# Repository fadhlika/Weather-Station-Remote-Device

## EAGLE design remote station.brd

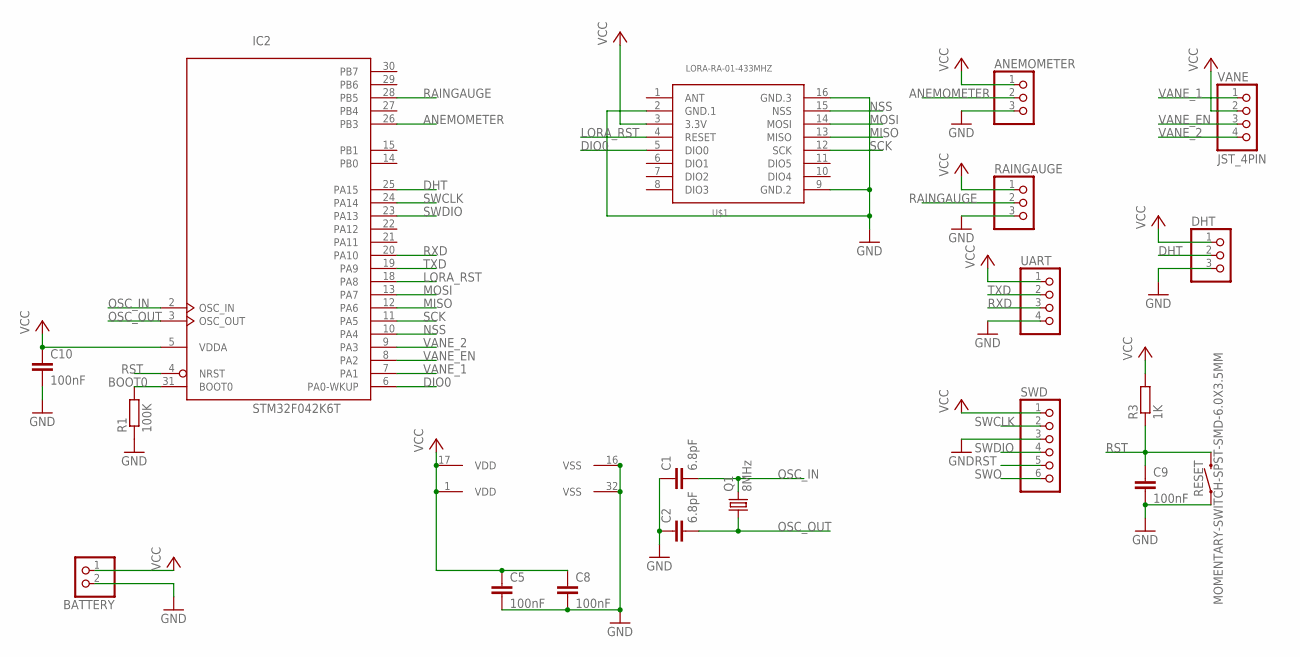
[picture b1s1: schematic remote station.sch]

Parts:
ANEMOMETER: JST_3PIN; JSTPH3
BATTERY: JST_2PIN-SMT-RA; JST-PH-2-SMT-RA
C1, C2: 6.8pF; C0805K
C5, C8, C9, C10: 100nF; C0805K
DHT: JST_3PIN; JSTPH3
IC2: STM32F042K6T; LQFP32
Q1: 8MHz; HC49UP
R1: 100K; R0805W
R3: 1K; R0805W
RAINGAUGE: JST_3PIN; JSTPH3
RESET: MOMENTARY-SWITCH-SPST-SMD-6.0X3.5MM; TACTILE_SWITCH_SMD_6.0X3.5MM
SWD: PINHD-1X6; 1X06
U$1: LORA-RA-01-433MHZ; LORA-RA1-SMD
UART: PINHD-1X4; 1X04
VANE: JST_4PIN; JST-PH-2-SMT-RA

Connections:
ANEMOMETER: ANEMOMETER.2, IC2.26 (PB3)
BOOT0: IC2.31 (BOOT0), R1.2
DHT: DHT.2, IC2.25 (PA15)
DIO0: IC2.6 (PA0-WKUP), U$1.5 (DIO0)
GND: ANEMOMETER.3, BATTERY.2 (1), C1.1, C2.1, C5.2, C8.2, C9.2, C10.2, DHT.3, IC2.16 (VSS), IC2.32 (VSS), R1.1, RAINGAUGE.3, RESET.1, SWD.3, U$1.2 (GND.1), U$1.9 (GND.2), U$1.16 (GND.3), UART.4
LORA_RST: IC2.18 (PA8), U$1.4 (RESET)
MISO: IC2.12 (PA6), U$1.13 (MISO)
MOSI: IC2.13 (PA7), U$1.14 (MOSI)
NSS: IC2.10 (PA4), U$1.15 (NSS)
OSC_IN: C1.2, IC2.2 (OSC_IN), Q1.2
OSC_OUT: C2.2, IC2.3 (OSC_OUT), Q1.1
RAINGAUGE: IC2.28 (PB5), RAINGAUGE.2
RST: C9.1, IC2.4 (NRST), R3.1, RESET.2, SWD.5
RXD: IC2.20 (PA10), UART.3
SCK: IC2.11 (PA5), U$1.12 (SCK)
SWCLK: IC2.24 (PA14), SWD.2
SWDIO: IC2.23 (PA13), SWD.4
SWO: SWD.6
TXD: IC2.19 (PA9), UART.2
VANE_1: IC2.7 (PA1), VANE.1
VANE_2: IC2.9 (PA3), VANE.4
VANE_EN: IC2.8 (PA2), VANE.3
VCC: ANEMOMETER.1, BATTERY.1 (2), C5.1, C8.1, C10.1, DHT.1, IC2.1 (VDD), IC2.5 (VDDA), IC2.17 (VDD), R3.2, RAINGAUGE.1, SWD.1, U$1.3 (3.3V), UART.1, VANE.2

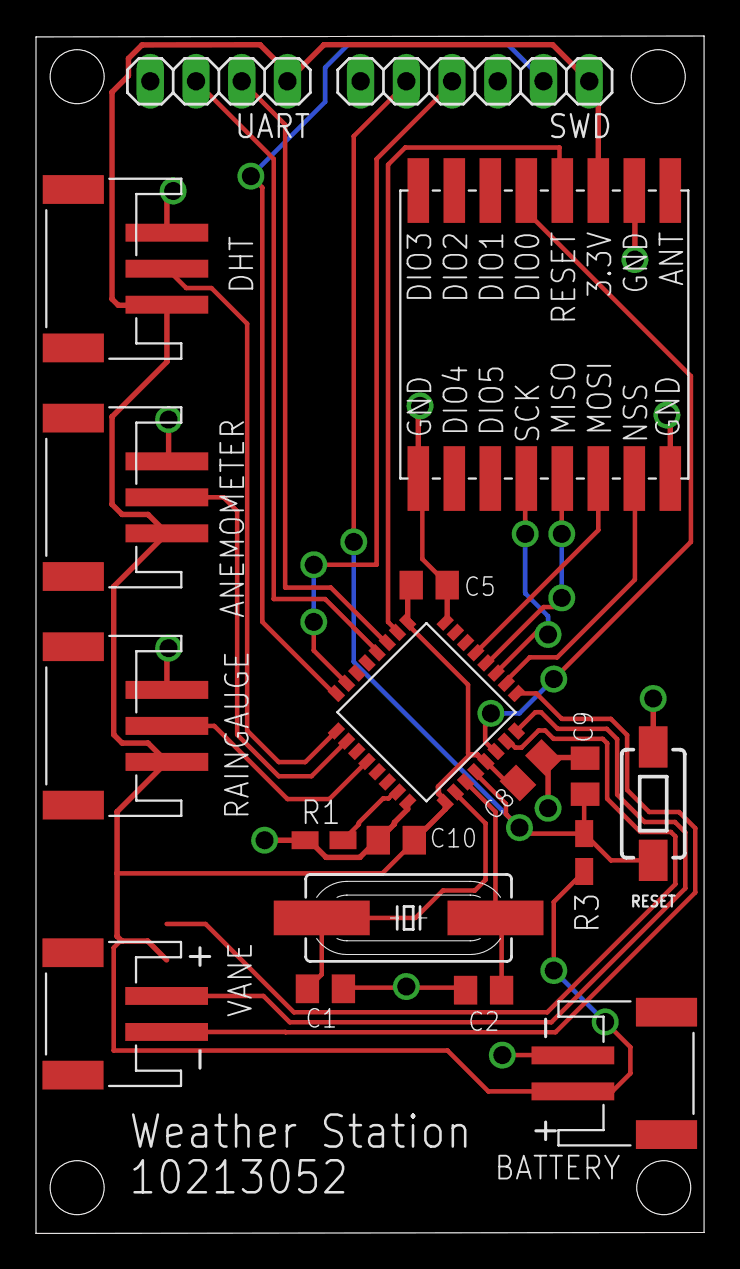
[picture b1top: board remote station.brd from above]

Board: 2 copper layers, 37.1 x 66.5 mm, 19 parts (0 on the bottom side), 22 nets.

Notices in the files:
parts and their libraries:
SparkFun-Switches: Licensing: Creative Commons ShareAlike 4.0 International - https://creativecommons.org/licenses/by-sa/4.0
